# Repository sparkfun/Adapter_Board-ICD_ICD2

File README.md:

SparkFun Adapter Board-ICD/ICD2
===============================

[*SparkFun Adapter Board- ICD/ICD2 (BOB-00193)*](https://www.sparkfun.com/products/193)

This is a small PCB that adapts the standard Microchip 
6-Pin RJ11 connector to the Olimex 6-Pin .1" Molex Connector.

Repository Contents
-------------------
* **/Hardware** - All Eagle design files (.brd, .sch, .STL)

License Information
-------------------
The hardware is released under [Creative Commons ShareAlike 4.0 International](https://creativecommons.org/licenses/by-sa/4.0/).

Distributed as-is; no warranty is given.

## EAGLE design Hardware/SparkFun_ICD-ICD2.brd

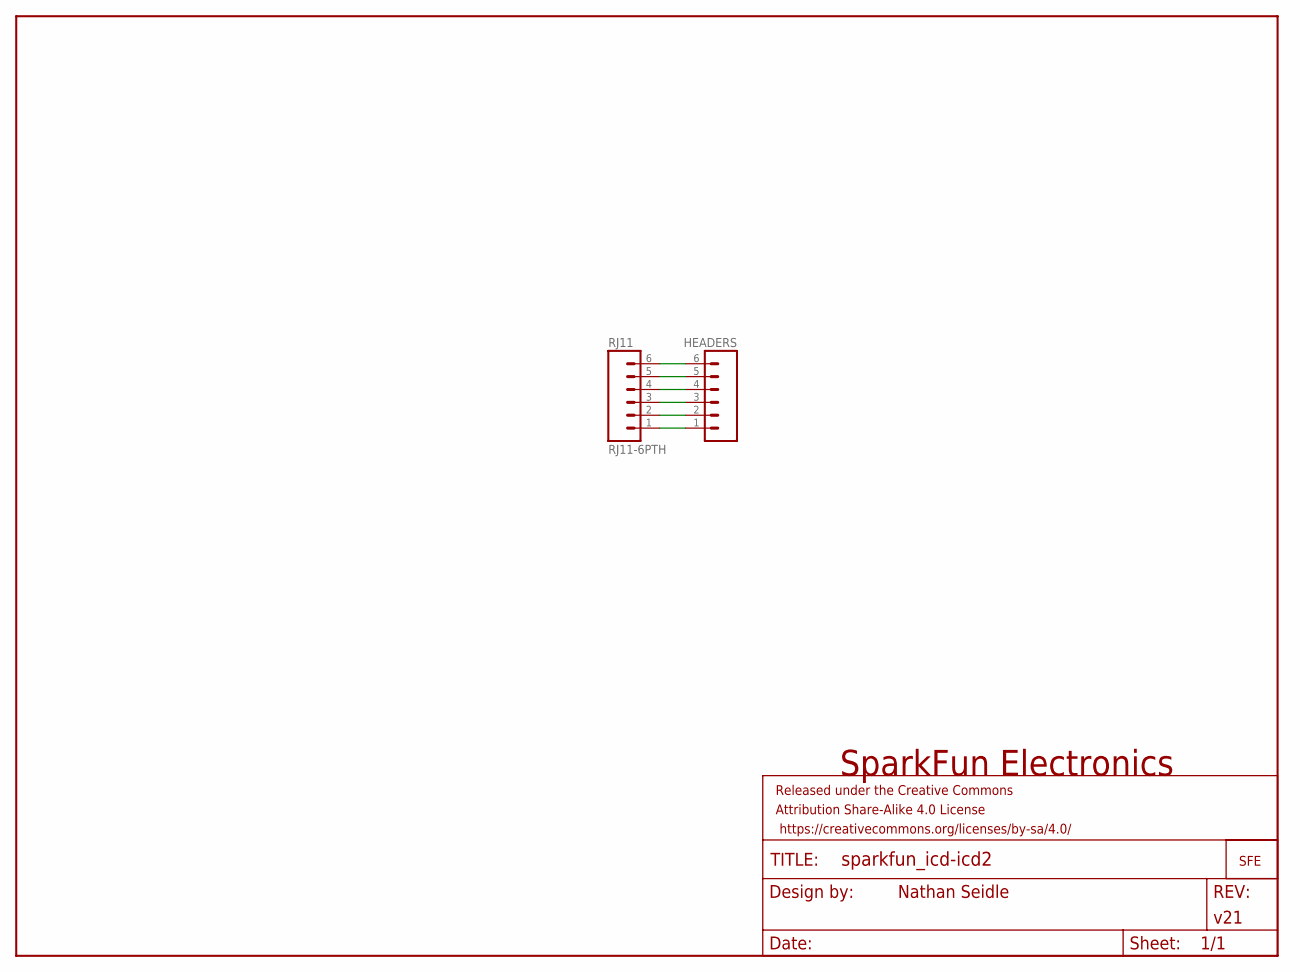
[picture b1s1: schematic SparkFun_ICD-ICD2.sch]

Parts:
FRAME1: FRAME-LETTERNO_PACKAGE; DUMMY
HEADERS: M06POLAR; MOLEX-1X6
JP1: LOGO-SFESK; SFE-LOGO-FLAME
RJ11: RJ11-6PTH; RJ11-6

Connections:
unnamed: HEADERS.6, RJ11.6
unnamed: HEADERS.1, RJ11.1
unnamed: HEADERS.2, RJ11.2
unnamed: HEADERS.3, RJ11.3
unnamed: HEADERS.4, RJ11.4
unnamed: HEADERS.5, RJ11.5

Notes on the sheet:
SparkFun Electronics

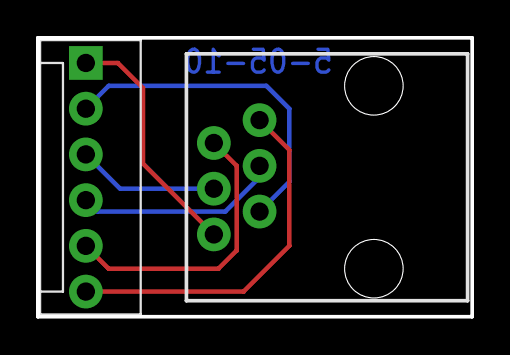
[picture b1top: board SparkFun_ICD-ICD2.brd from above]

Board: 2 copper layers, 24.1 x 15.5 mm, 4 parts (1 on the bottom side), 6 nets.

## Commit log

2015-01-29 Initial hardware file commit

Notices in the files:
parts and their libraries:
SparkFun-Aesthetics: Licensing: Creative Commons ShareAlike 4.0 International - https://creativecommons.org/licenses/by-sa/4.0
SparkFun-Aesthetics: Released under the Creative Commons Attribution Share-Alike 4.0 License
SparkFun-Aesthetics: Released under the Creative Commons
